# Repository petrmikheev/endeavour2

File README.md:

Endeavour2
==========

This is the second generation of my FPGA board.
Comparing to [endeavour1](https://github.com/petrmikheev/endeavour) it is 4 times faster and has 8x more memory.

The goal was the same as on the previous iteration -- to make a DIY computer based on FPGA. It should support display, keyboard, should be able to run Linux, should have on-device compiler toolchain, and ideally should be able to render some 3D graphic. It was fully achieved -- I have even managed to connect my board to WiFi and play Quake2 in multiplayer.

The project includes several parts:

- Hardware: design PCB and make the board. I ordered PCB manufacturing in JLCPCB, soldering is done manually.
- RTL: design SoC for my FPGA board. It is mostly assembled from open source IP cores, but some components are implemented from scratch.
- Firmware: written from scratch (except of integrated Dhrystone benchmark), includes initialization code, memtest, sbi implemetation, ext2 filesystem support, linux bootloader, built-in console. Provides some API (e.g printf) for software running in M-mode.
- Linux drivers for custom peripherals.
- Custom window manager and TTY implementation.

Note: This is a hobby project created just for fun. It doesn't have much practical use. However, if for some reason somebody wants to make a copy of this FPGA board, please let me know. I might add a bit more documentation.

Here's a story about how I worked on the project: **[https://blog.mikhe.ch/quake2-on-fpga](https://blog.mikhe.ch/quake2-on-fpga)**.

License: GPL-3.0 (except of footprints in hardware/endeavour2.pretty and Dhrystone benchmark in software/bios/dhrystone)

## Hardware

Main changes comparing to [endeavour1](https://github.com/petrmikheev/endeavour):

- This time I took a chance with BGA (Ball Grid Array) chips, and surprisingly soldering was not as hard as I expected.
- Using Efinix FPGA [Ti60F256](https://www.efinixinc.com/shop/ti60.php) with 60K logic cells and 256 1024x10b memory blocks. VexiiRiscv runs on this chip at frequency 207 MHz -- quite a lot for FPGA, especially in comparison to 60 MHz which I previously got with Altera Max10.
- 1GB DDR3 RAM IM8G16D3FFBG (against 128MB DDR1 in endeavour1). I use Efinix DDR3 Soft Controller Core. Using DDR3-400 mode, 800 MT/s, max theoretical throughput 1.6 GB/s. In practice in benchmarks I get up to 1.1 GB/s.
- Implemented SD Card voltage switch 3.3V/1.8V. In theory it allows to use UHS-1 cards in SDR104 mode (up to 100 MB/s), but for some cards writes failed at this speed, so I use SDR50 (46 MB/s in benchmark).
- Added a specialized TMDS encoder TFP410 (in endeavour1 video output was driven directly by FPGA pins which provided not enough current and caused green artifacts in some cases). Now all display modes with pixel rate up to 165 MHz are supported.
- More capacitors and a current limiting scheme on USB ports. USB hotplug can not cause device reset anymore!
- Added a real time clock in order not to appear in 1970 every time I start linux.
- Added ESP32 module as a WiFi adapter. `wget` shows download speed 926 KB/s.
- Added 2000mAh LiPo battery. 
- Added 4.2'' E-Ink display.

[KiCad project](hardware/board_2b), [gerber files](hardware/board_2b/production/endeavour2.zip).

**PCB production details ([JLCPCB](https://jlcpcb.com/capabilities/pcb-capabilities))**

- 6 layers
- Stackup: JLC06161H-3313
- Min via hole/diameter: 0.2/0.35mm
- Via covering: epoxy filled & capped

---

Endeavour2a (above) and Endeavour2b (below).

### Known design errors

In Endeavour2a:

- D+ and D- lines on USB-C port A are accidentally swapped, so port A can be used only as a power source. There are two USB-C ports because I was not sure that USB connection to PC will give enough power, and added a second USB-C for a power adapter. It turned out to be unnecessary, so in Endeavour2b the second port is removed.
- ESP32 connection scheme includes not all the pins which are needed for [ESP-Hosted-NG](https://github.com/espressif/esp-hosted/blob/master/esp_hosted_ng/README.md) firmware. I tried to remap some pins, but it caused extra delays and SPI transfers didn't work properly. So Endeavour2a has no WiFi. Fixed in Endeavour2b.

In Endeavour2b:

- Using same DC-DC converters as in Endeavour2a (TPS562211) to generate 0.95V, 1.35V, 1.8V. I forgot that it requires input power at least 4.2V and can work from USB (which was the case in Endeavour2a), but not from a battery pack. So the device can use battery power only when the battery is fully charged. Will be fixed in Endeavour2c.

### 3d printed case

---

## RTL

Used IP cores:

- [VexiiRiscv](https://github.com/SpinalHDL/VexiiRiscv/) - RISC-V core written in SpinalHDL.
- A few components distributed with [SpinalHDL](https://github.com/SpinalHDL/SpinalHDL) including Tilelink interconnect, APB3 bridge, USB OHCI controller, PLIC.
- [ZipCPU/sdspi SD-Card controller](https://github.com/ZipCPU/sdspi).
- [Efinix DDR3 Soft Controller Core](https://www.efinixinc.com/support/ip/ddr3-controller.php) (source not available, can be used only with Efinix FPGAs).

All the other components are designed from scratch.
DDR3 Tilelink adapter, UART controller, I2C controller, audio controller, SPI controllers (SPI FLASH, ESP32 SPI, and E2417 SPI interfaces have different requirements, so I end up with 3 different SPI controllers optimized for specific use cases), etc. Most notable are video controller and DMA controller.

[SpinalHDL](https://github.com/SpinalHDL/SpinalHDL) is being used to bring this all together.

### Video controller

- Has idependent text and graphic layers with transparency support.
- Configurable video timings.
- Supports both vertical (with wraparound) and horizontal panning.
- Graphic layer uses RGB565 format.
- Text layer has configurable charmap with 480 entries - e.g. ASCII + bold + italic variations + pseudographics can be loaded at the same time. Supports bitmap fonts with sizes from 8x8 to 8x16. Supports special 4-color symbols mode (used to render Endeavour logo, see screenshots below).
- APB3 control interface, Tilelink DMA interface.
- Implemented in verilog. [source](rtl/verilog/video_controller.v)
- There is [linux driver](software/linux/drivers/display.c). See usage in [include/endeavour2/display.h](software/include/endeavour2/display.h).

### DMA controller

- Can execute multiple memory operations by a single batch request from CPU (needed e.g. for hardware-accelerated window move in X11 since each line requires separate copying).
- Supports unaligned memset and memcpy (also essential for window move).
- Supports some graphics-related instructions: batched RGB565 mixing and palette mapping. So it is kind of a very primitive 2D GPU. I used it to speedup rendering in Quake2.
- APB3 control interface, Tilelink DMA interface.
- Implemented in SpinalHDL. [source](rtl/src/main/scala/endeavour2/DmaController.scala)

## Software

### [software/bios](software/bios)

Firmware. Initialization, benchmarks, sbi, bootloader, etc. Loaded on boot from SPI flash or via UART.

BIOS console allows to either boot OS (switches to supervisor mode), or inspect files (only EXT2 supported) and run binaries in machine mode.

BIOS provides API: [bios.h](software/include/endeavour2/raw/bios.h)

Example that uses this API: [hello_world.c](software/raw_examples/hello_world.c)

### [software/textwm2](software/textwm2)

Text-layer window manager and TTY implementation.

---

**wget 926 KB/s**, ESP32 as WiFi/BT adapter.

### [software/linux](software/linux)

Linux kernel config and drivers.

### [software/buildroot](software/buildroot)

Buildroot config and a few related scripts.

### [xdriver-endeavour2-fbdev](software/buildroot/xdriver-endeavour2-fbdev)

X11 driver which uses DMA controller when moving windows.

### [quake2sdl.patch](software/buildroot/quake2sdl.patch)

Patch for [quake2sdl](https://github.com/shamazmazum/quake2sdl).

- Using DMA controller for hardware-accelerated mapping from 256 colors to RGB565, and bilinear upscaling.
- Migrated from SDL audio to a custom endeavour2 driver with lower overhead (overhead of ALSA subsystem was quite significant).
- Downgraded from SDL2 to SDL1 (so it can run without X11).

Average FPS 12.2 on demo1 map with resolution 640x360 and bilinear upscaling to 1280x720.

### A few more screenshots

---

**DOOM**

---

**Quake 1**

---

**Heroes2**

---

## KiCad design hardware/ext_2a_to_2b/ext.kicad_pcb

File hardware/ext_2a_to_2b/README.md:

It is extension for `board_2a` to test some parts of `board_2b` schematics

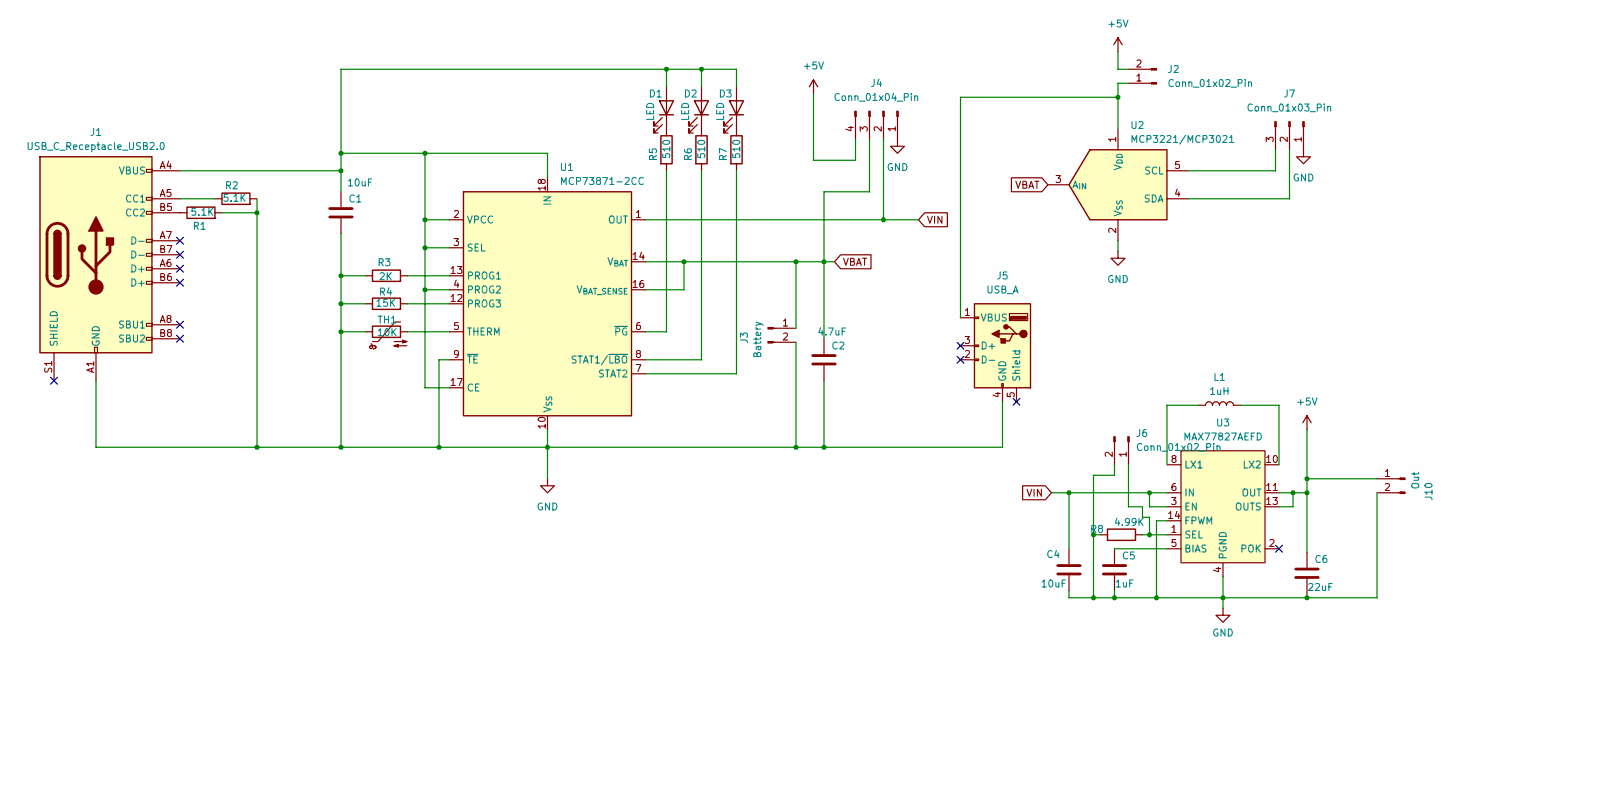
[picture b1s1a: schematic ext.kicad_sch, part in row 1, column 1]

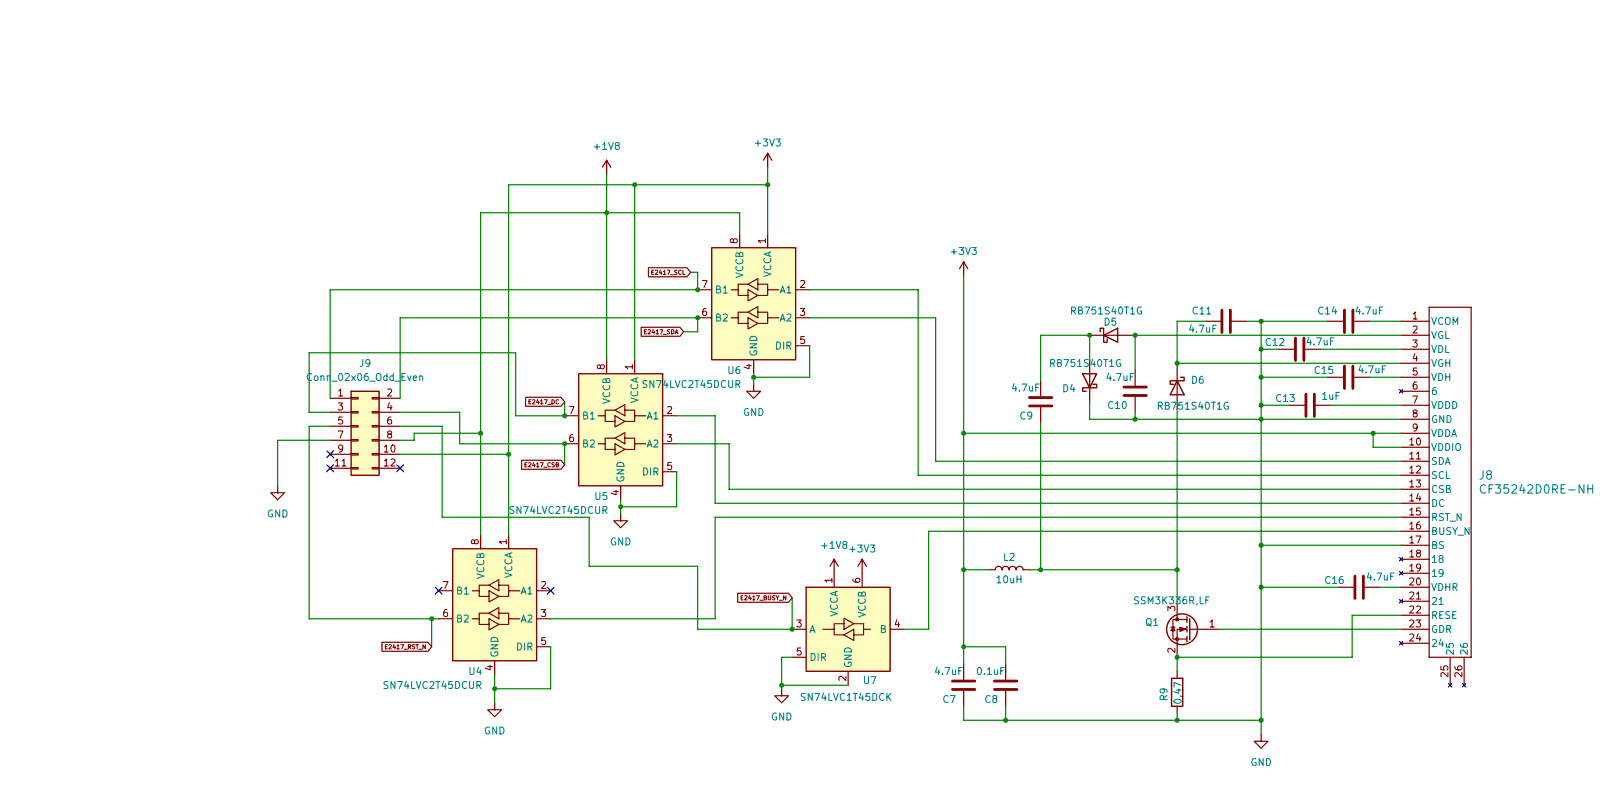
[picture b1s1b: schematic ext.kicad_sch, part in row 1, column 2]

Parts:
C1, C4: 10uF; C_0603_1608Metric
C2, C7, C9, C10, C11, C12, C14, C15, C16: 4.7uF; C_0603_1608Metric
C5, C13: 1uF; C_0603_1608Metric
C6: 22uF; C_0805_2012Metric
C8: 0.1uF; C_0603_1608Metric
D1, D2, D3: LED; LED_0603_1608Metric
D4, D5, D6: RB751S40T1G; D_SOD-523
J1: USB_C_Receptacle_USB2.0; USB_C_Receptacle_GCT_USB4105-xx-A_16P_TopMnt_Horizontal
J2, J6: Conn_01x02_Pin; PinHeader_1x02_P2.54mm_Vertical
J3: Battery; JST_B2B-PH-SM4-TB
J4: Conn_01x04_Pin; PinHeader_1x04_P2.54mm_Vertical
J5: USB_A; USB_A_Receptacle_GCT_USB1046
J7: Conn_01x03_Pin; PinHeader_1x03_P2.54mm_Vertical
J8: CF35242D0RE-NH; CONN24X1_CF35242D0RE-NH_CVI
J9: Conn_02x06_Odd_Even; PinHeader_2x06_P2.54mm_Vertical
J10: Out; JST_B2B-PH-SM4-TB
L1: 1uH; L_0805_2012Metric
L2: 10uH; L_0805_2012Metric
Q1: SSM3K336R,LF; SOT-23-3
R1, R2: 5.1K; R_0603_1608Metric
R3: 2K; R_0603_1608Metric
R4: 15K; R_0603_1608Metric
R5, R6, R7: 510; R_0603_1608Metric
R8: 4.99K; R_0603_1608Metric
R9: 0.47; R_0603_1608Metric
TH1: 10K; R_0603_1608Metric
U1: MCP73871-2CC; QFN-20-1EP_4x4mm_P0.5mm_EP2.5x2.5mm
U2: MCP3221/MCP3021; SOT-23-5
U3: MAX77827AEFD; Maxim_FC2QFN-14_2.5x2.5mm_P0.5mm
U4, U5, U6: SN74LVC2T45DCUR; VSSOP-8_2.3x2mm_P0.5mm
U7: SN74LVC1T45DCK; SOT-363_SC-70-6

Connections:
+1V8: J9.8, U4.8 (VCCB), U5.8 (VCCB), U6.8 (VCCB), U7.1 (VCCA)
+3V3: C7.2, C8.2, J8.9 (VDDA), J8.10 (VDDIO), J9.10, L2.1, U4.1 (VCCA), U5.1 (VCCA), U6.1 (VCCA), U7.6 (VCCB)
+5V: C6.1, J2.2, J4.4, J10.1, U3.11 (OUT), U3.13 (OUTS)
E2417_BUSY_N: J9.6, U7.3 (A)
E2417_CSB: J9.4, U5.6 (B2)
E2417_DC: J9.3, U5.7 (B1)
E2417_RST_N: J9.5, U4.6 (B2)
E2417_SCL: J9.1, U6.7 (B1)
E2417_SDA: J9.2, U6.6 (B2)
GND: C1.2, C2.2, C4.2, C5.2, C6.2, C7.1, C8.1, C10.1, C11.1, C12.1, C13.1, C14.1, C15.1, C16.1, D4.1 (K), J1.A1 (GND), J1.A12 (GND), J1.B1 (GND), J1.B12 (GND), J3.2, J4.1, J5.4 (GND), J6.2, J7.1, J8.8 (GND), J8.17 (BS), J9.7, J10.2, R1.2, R2.2, R3.1, R4.1, R8.1, R9.1, TH1.1, U1.9 (~TE), U1.10 (V_{SS}), U1.11 (V_{SS}), U1.21 (V_{SS}), U2.2 (V_{SS}), U3.4 (PGND), U3.9 (PGND), U3.14 (FPWM), U4.4 (GND), U4.5 (DIR), U5.4 (GND), U5.5 (DIR), U6.4 (GND), U6.5 (DIR), U7.2 (GND), U7.5 (DIR)
unnamed: C1.1, D1.2 (A), D2.2 (A), D3.2 (A), J1.A4 (VBUS), J1.A9 (VBUS), J1.B4 (VBUS), J1.B9 (VBUS), U1.2 (VPCC), U1.3 (SEL), U1.4 (PROG2), U1.17 (CE), U1.18 (IN), U1.19 (IN)
unnamed: D1.1 (K), R5.1
unnamed: D2.1 (K), R6.1
unnamed: D3.1 (K), R7.1
unnamed: C9.2, D4.2 (A), D5.1 (K)
unnamed: C10.2, D5.2 (A), J8.2 (VGL)
unnamed: C9.1, D6.2 (A), L2.2, Q1.3 (D)
unnamed: C11.2, D6.1 (K), J8.4 (VGH)
unnamed: J1.A5 (CC1), R2.1
unnamed: J1.B5 (CC2), R1.1
unnamed: J2.1, J5.1 (VBUS), U2.1 (V_{DD})
unnamed: J6.1, R8.2, U3.1 (SEL)
unnamed: J7.2, U2.4 (SDA)
unnamed: J7.3, U2.5 (SCL)
unnamed: J8.16 (BUSY_N), U7.4 (B)
unnamed: J8.13 (CSB), U5.3 (A2)
unnamed: J8.14 (DC), U5.2 (A1)
unnamed: J8.23 (GDR), Q1.1 (G)
unnamed: J8.22 (RESE), Q1.2 (S), R9.2
unnamed: J8.15 (RST_N), U4.3 (A2)
unnamed: J8.12 (SCL), U6.2 (A1)
unnamed: J8.11 (SDA), U6.3 (A2)
unnamed: C14.2, J8.1 (VCOM)
unnamed: C13.2, J8.7 (VDDD)
unnamed: C15.2, J8.5 (VDH)
unnamed: C16.2, J8.20 (VDHR)
unnamed: C12.2, J8.3 (VDL)
unnamed: R3.2, U1.13 (PROG1)
unnamed: R4.2, U1.12 (PROG3)
unnamed: R6.2, U1.8 (STAT1/~LBO)
unnamed: R7.2, U1.7 (STAT2)
unnamed: TH1.2, U1.5 (THERM)
unnamed: R5.2, U1.6 (~PG)
unnamed: C5.1, U3.5 (BIAS)
unnamed: L1.1, U3.8 (LX1)
unnamed: L1.2, U3.10 (LX2)
VBAT: C2.1, J3.1, J4.3, U1.14 (V_{BAT}), U1.15 (V_{BAT}), U1.16 (V_{BAT_SENSE}), U2.3 (A_{IN})
VIN: C4.1, J4.2, U1.1 (OUT), U1.20 (OUT), U3.3 (EN), U3.6 (IN)

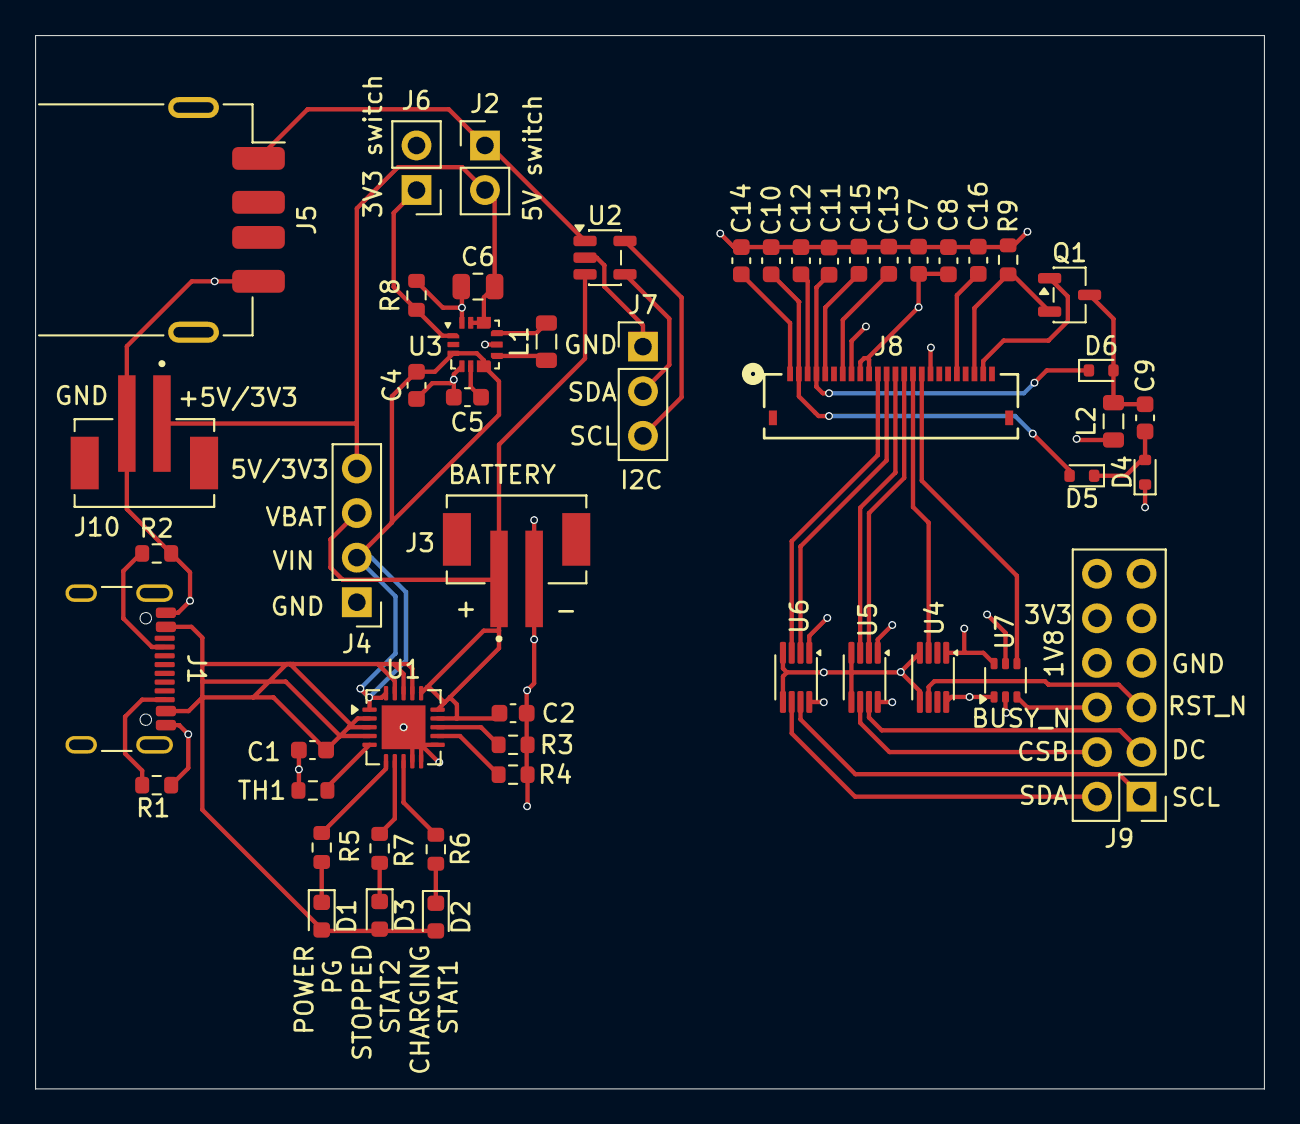
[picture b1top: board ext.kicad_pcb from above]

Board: 4 copper layers, 70.0 x 60.0 mm, 51 parts (0 on the bottom side), 48 nets.

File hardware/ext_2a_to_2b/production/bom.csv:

Designator,Footprint,Quantity,Value,LCSC Part #
"C1, C4",0603,2,10uF,
"C10, C11, C12, C14, C15, C16, C2, C7, C9",0603,9,4.7uF,
"C13, C5",0603,2,1uF,
C6,0805,1,22uF,
C8,0603,1,0.1uF,
"D1, D2, D3",0603,3,LED,
"D4, D5, D6",D_SOD-523,3,RB751S40T1G,
J1,USB_C_Receptacle_GCT_USB4105-xx-A_16P_TopMnt_Horizontal,1,USB_C_Receptacle_USB2.0,
J10,JST_B2B-PH-SM4-TB,1,Out,
"J2, J6",PinHeader_1x02_P2.54mm_Vertical,2,Conn_01x02_Pin,
J3,JST_B2B-PH-SM4-TB,1,Battery,
J4,PinHeader_1x04_P2.54mm_Vertical,1,Conn_01x04_Pin,
J5,USB_A_Receptacle_GCT_USB1046,1,USB_A,
J7,PinHeader_1x03_P2.54mm_Vertical,1,Conn_01x03_Pin,
J8,CONN24X1_CF35242D0RE-NH_CVI,1,CF35242D0RE-NH,
J9,PinHeader_2x06_P2.54mm_Vertical,1,Conn_02x06_Odd_Even,
L1,0805,1,1uH,
L2,0805,1,10uH,
Q1,SOT-23-3,1,"SSM3K336R,LF",
"R1, R2",0603,2,5.1K,
R3,0603,1,2K,
R4,0603,1,15K,
"R5, R6, R7",0603,3,510,
R8,0603,1,4.99K,
R9,0603,1,0.47,
TH1,0603,1,10K,
U1,QFN-20-1EP_4x4mm_P0.5mm_EP2.5x2.5mm,1,MCP73871-2CC,
U2,SOT-23-5,1,MCP3221/MCP3021,
U3,Maxim_FC2QFN-14_2.5x2.5mm_P0.5mm,1,MAX77827AEFD,
"U4, U5, U6",VSSOP-8_2.3x2mm_P0.5mm,3,SN74LVC2T45DCUR,
U7,SOT-363_SC-70-6,1,SN74LVC1T45DCK,

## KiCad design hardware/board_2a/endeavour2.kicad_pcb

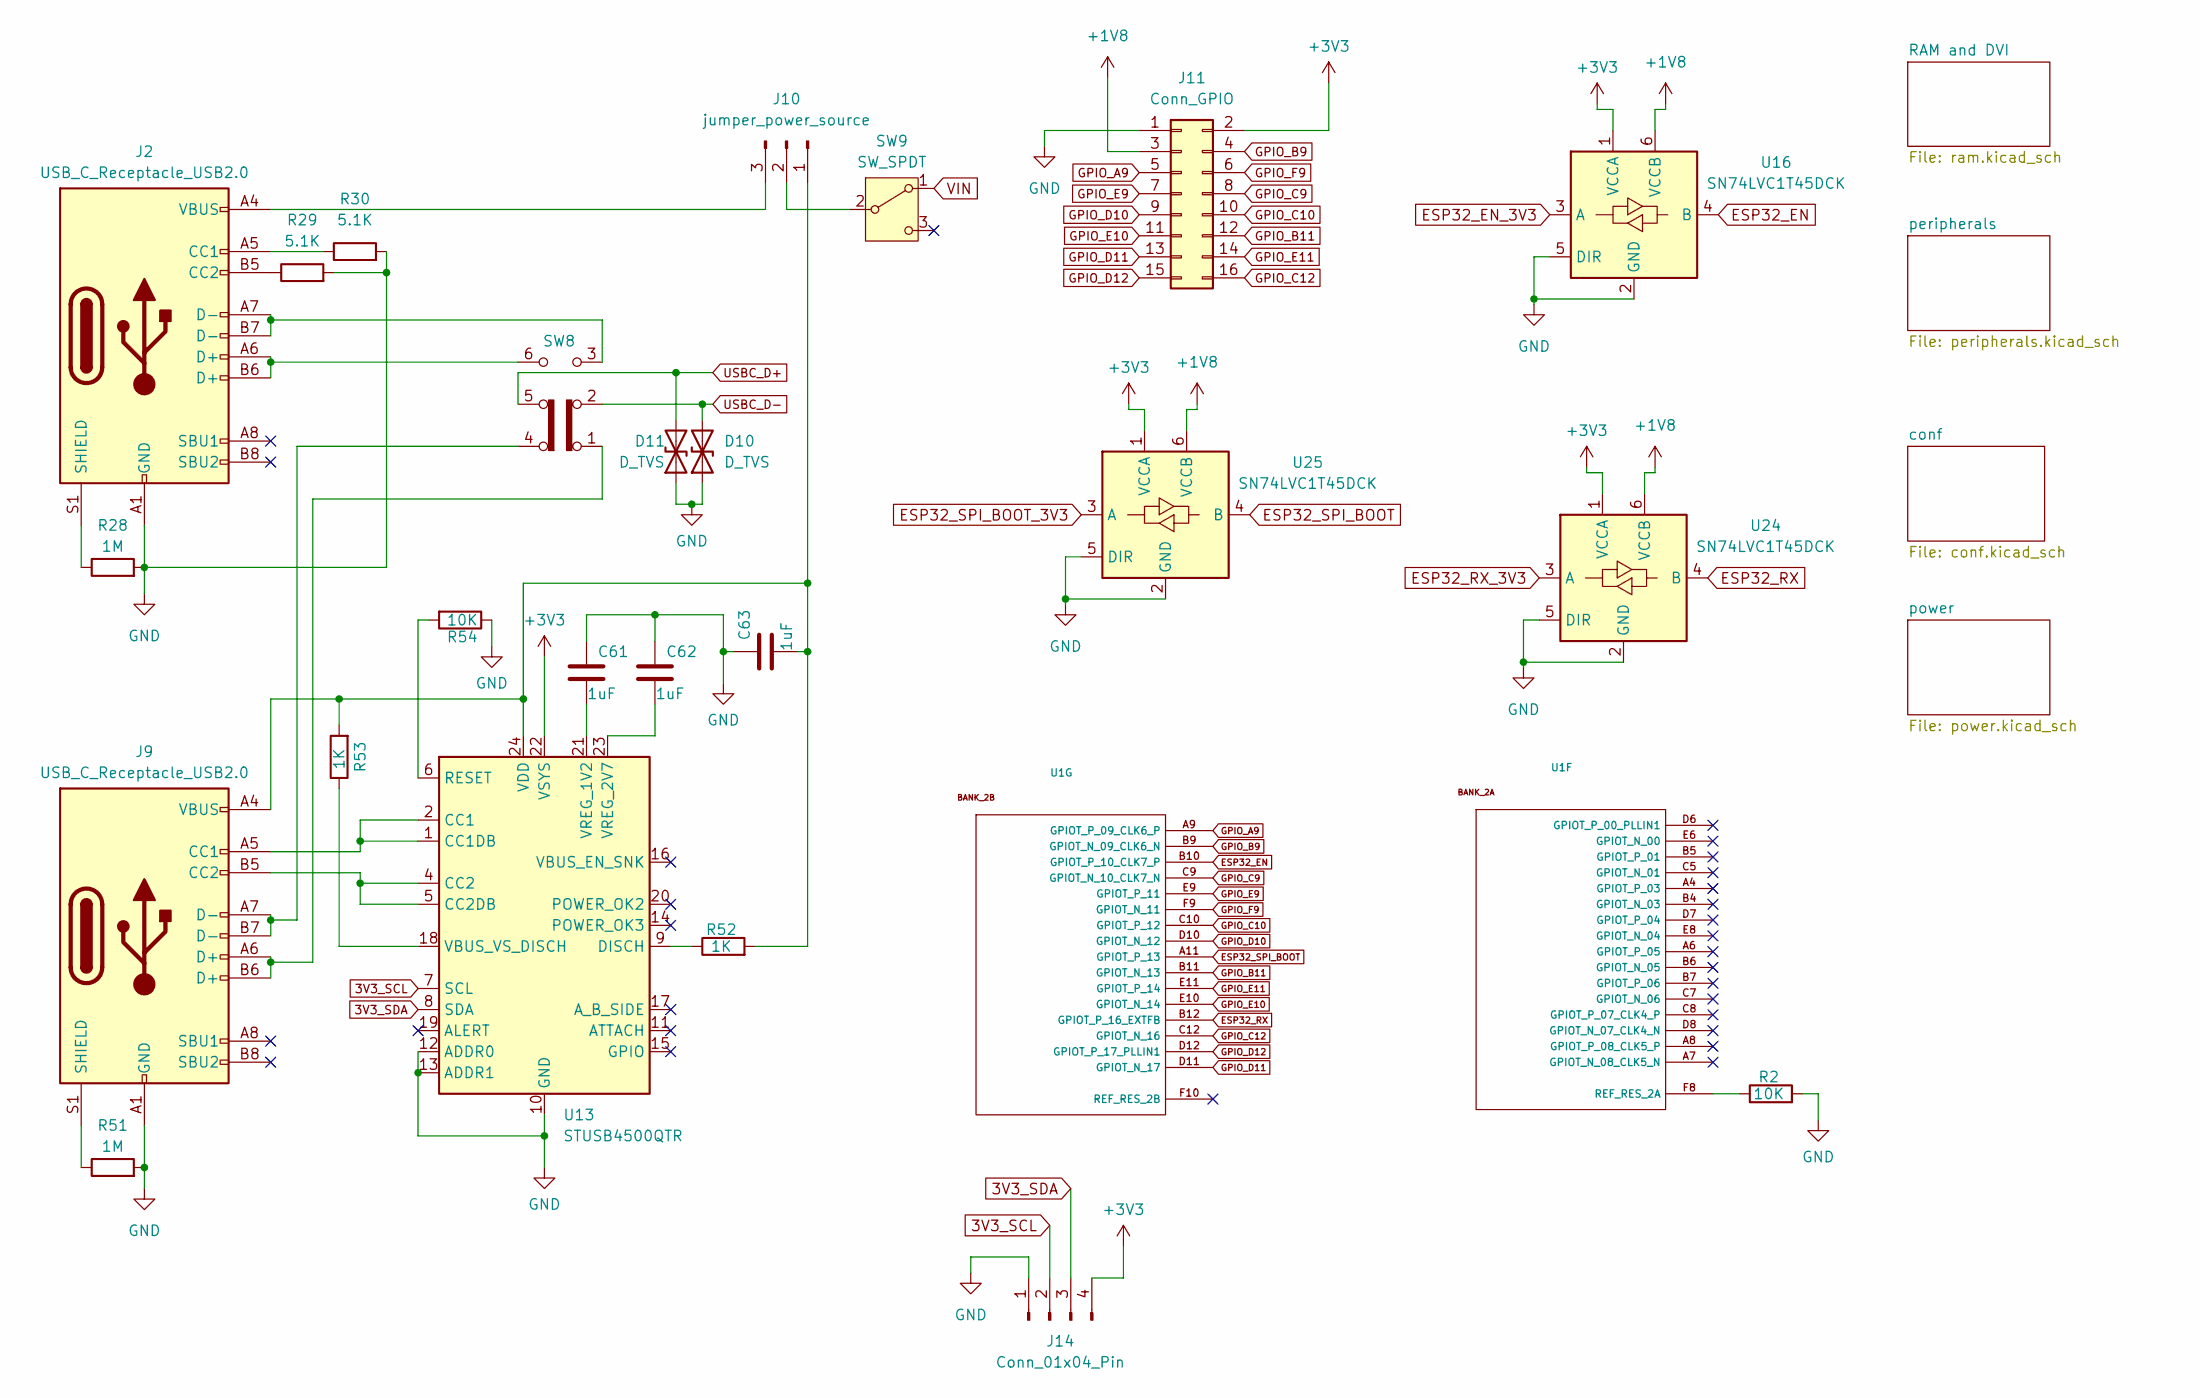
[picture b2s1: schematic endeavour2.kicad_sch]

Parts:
C61, C62, C63: 1uF; C_0603_1608Metric
D10, D11: D_TVS; D_0603_1608Metric
J2, J9: USB_C_Receptacle_USB2.0; USB_C_Receptacle_GCT_USB4105-xx-A_16P_TopMnt_Horizontal
J10: jumper_power_source; PinHeader_1x03_P2.54mm_Vertical
J11: Conn_GPIO; PinHeader_2x08_P2.54mm_Vertical
J14: Conn_01x04_Pin; PinHeader_1x04_P2.54mm_Vertical
R2, R54: 10K; R_0603_1608Metric
R28, R51: 1M; R_0603_1608Metric
R29, R30: 5.1K; R_0603_1608Metric
R52, R53: 1K; R_0603_1608Metric
SW8: SW_JS202011SCQN
SW9: SW_SPDT; mss3111
U1: Ti60F256; BGA-256_14.0x14.0mm_Layout16x16_P0.8mm_Ball0.45mm_Pad0.32mm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
U13: STUSB4500QTR; QFN-24-1EP_4x4mm_P0.5mm_EP2.7x2.7mm
U16, U24, U25: SN74LVC1T45DCK; SOT-363_SC-70-6

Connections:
3V3_SCL: J14.2, U13.7 (SCL); also elsewhere on the board
3V3_SDA: J14.3, U13.8 (SDA); also elsewhere on the board
+1V8: J11.3, U16.6 (VCCB), U24.6 (VCCB), U25.6 (VCCB); also elsewhere on the board
+3V3: J11.2, J14.4, U13.22 (VSYS), U16.1 (VCCA), U24.1 (VCCA), U25.1 (VCCA); also elsewhere on the board
ESP32_EN: U1.B10 (GPIOT_P_10_CLK7_P), U16.4 (B)
ESP32_EN_3V3: U16.3 (A); also elsewhere on the board
ESP32_RX: U1.B12 (GPIOT_P_16_EXTFB), U24.4 (B)
ESP32_RX_3V3: U24.3 (A); also elsewhere on the board
ESP32_SPI_BOOT: U1.A11 (GPIOT_P_13), U25.4 (B)
ESP32_SPI_BOOT_3V3: U25.3 (A); also elsewhere on the board
GND: C61.1, C62.1, C63.1, D10.1 (A1), D11.1 (A1), J2.A1 (GND), J2.A12 (GND), J2.B1 (GND), J2.B12 (GND), J9.A1 (GND), J9.A12 (GND), J9.B1 (GND), J9.B12 (GND), J11.1, J14.1, R2.2, R28.2, R29.2, R30.2, R51.2, R54.1, U13.10 (GND), U13.12 (ADDR0), U13.13 (ADDR1), U13.25 (GND), U16.2 (GND), U16.5 (DIR), U24.2 (GND), U24.5 (DIR), U25.2 (GND), U25.5 (DIR); also elsewhere on the board
GPIO_A9: J11.5, U1.A9 (GPIOT_P_09_CLK6_P)
GPIO_B9: J11.4, U1.B9 (GPIOT_N_09_CLK6_N)
GPIO_B11: J11.12, U1.B11 (GPIOT_N_13)
GPIO_C9: J11.8, U1.C9 (GPIOT_N_10_CLK7_N)
GPIO_C10: J11.10, U1.C10 (GPIOT_P_12)
GPIO_C12: J11.16, U1.C12 (GPIOT_N_16)
GPIO_D10: J11.9, U1.D10 (GPIOT_N_12)
GPIO_D11: J11.13, U1.D11 (GPIOT_N_17)
GPIO_D12: J11.15, U1.D12 (GPIOT_P_17_PLLIN1)
GPIO_E9: J11.7, U1.E9 (GPIOT_P_11)
GPIO_E10: J11.11, U1.E10 (GPIOT_N_14)
GPIO_E11: J11.14, U1.E11 (GPIOT_P_14)
GPIO_F9: J11.6, U1.F9 (GPIOT_N_11)
unnamed: J2.A5 (CC1), R30.1
unnamed: J2.B5 (CC2), R29.1
unnamed: J2.A6 (D+), J2.B6 (D+), SW8.6 (A)
unnamed: J2.A7 (D-), J2.B7 (D-), SW8.3 (C)
unnamed: J2.S1 (SHIELD), R28.1
unnamed: J9.A5 (CC1), U13.1 (CC1DB), U13.2 (CC1)
unnamed: J9.B5 (CC2), U13.4 (CC2), U13.5 (CC2DB)
unnamed: J9.A6 (D+), J9.B6 (D+), SW8.1 (A)
unnamed: J9.A7 (D-), J9.B7 (D-), SW8.4 (C)
unnamed: J9.S1 (SHIELD), R51.1
unnamed: C63.2, J9.A4 (VBUS), J9.A9 (VBUS), J9.B4 (VBUS), J9.B9 (VBUS), J10.1, R52.2, R53.2, U13.24 (VDD)
unnamed: J10.2, SW9.2 (B)
unnamed: J2.A4 (VBUS), J2.A9 (VBUS), J2.B4 (VBUS), J2.B9 (VBUS), J10.3
unnamed: R2.1, U1.F8 (REF_RES_2A)
unnamed: R52.1, U13.9 (DISCH)
unnamed: R54.2, U13.6 (RESET)
unnamed: R53.1, U13.18 (VBUS_VS_DISCH)
unnamed: C61.2, U13.21 (VREG_1V2)
unnamed: C62.2, U13.23 (VREG_2V7)
USBC_D+: D11.2 (A2), SW8.5 (B); also elsewhere on the board
USBC_D-: D10.2 (A2), SW8.2 (B); also elsewhere on the board
VIN: SW9.1 (A); also elsewhere on the board

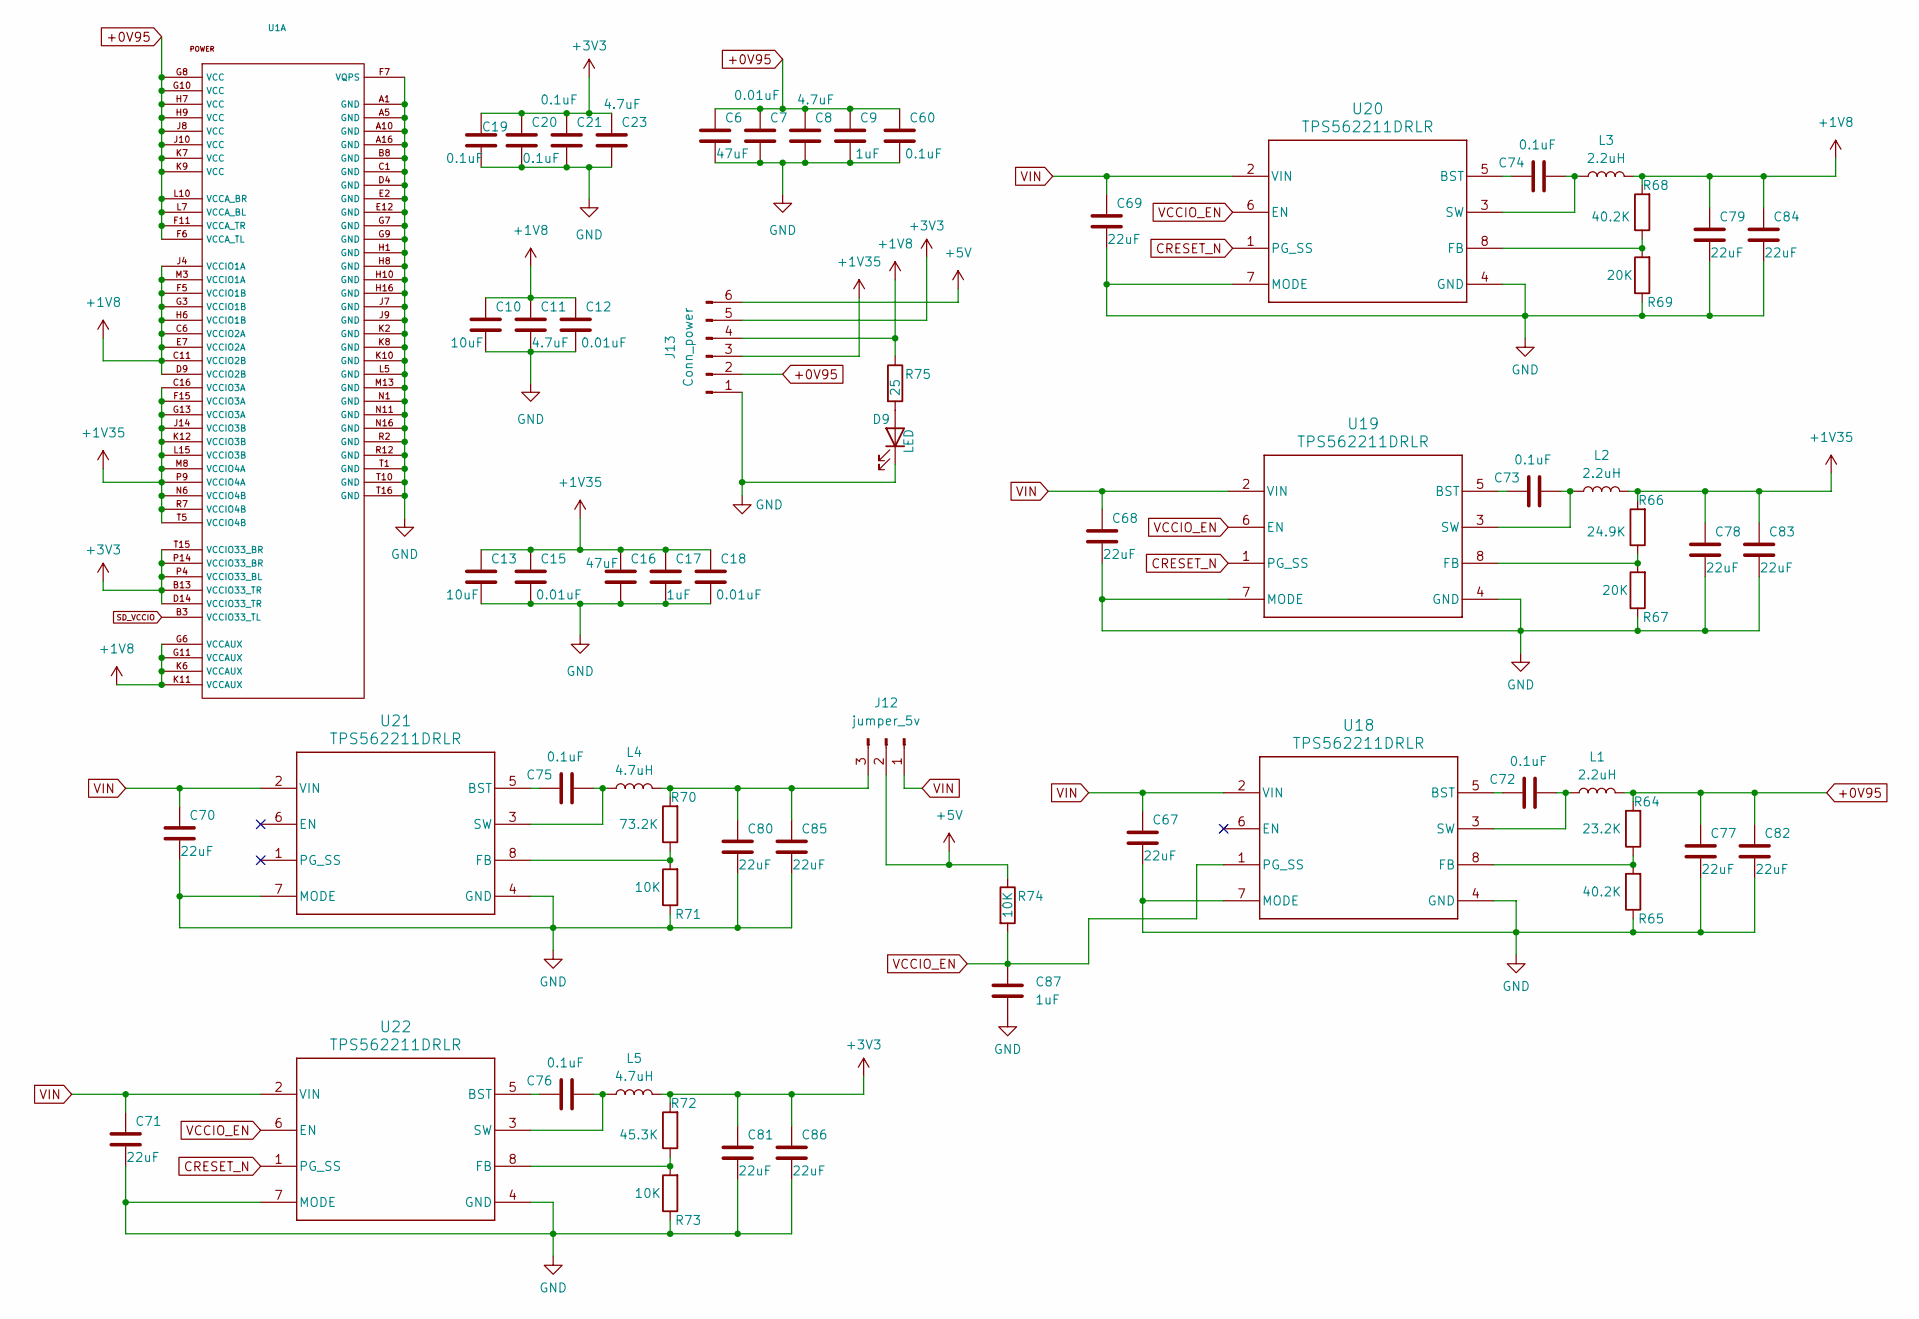
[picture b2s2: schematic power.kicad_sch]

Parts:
C6, C16: 47uF; C_0603_1608Metric
C7, C12, C15, C18: 0.01uF; C_0603_1608Metric
C8, C11, C23: 4.7uF; C_0603_1608Metric
C9, C17, C87: 1uF; C_0603_1608Metric
C10, C13: 10uF; C_0603_1608Metric
C19, C20, C21, C60, C72, C73, C74, C75, C76: 0.1uF; C_0603_1608Metric
C67, C68, C69, C70, C71, C77, C78, C79, C80, C81, C82, C83, C84, C85, C86: 22uF; C_0805_2012Metric
D9: LED; LED_0603_1608Metric
J12: jumper_5v; PinHeader_1x03_P2.54mm_Vertical
J13: Conn_power; PinHeader_1x06_P2.54mm_Vertical
L1, L2, L3: 2.2uH; L_1008_2520Metric
L4, L5: 4.7uH; L_1008_2520Metric
R64: 23.2K; R_0603_1608Metric
R65, R68: 40.2K; R_0603_1608Metric
R66: 24.9K; R_0603_1608Metric
R67, R69: 20K; R_0603_1608Metric
R70: 73.2K; R_0603_1608Metric
R71, R73, R74: 10K; R_0603_1608Metric
R72: 45.3K; R_0603_1608Metric
R75: 25; R_0603_1608Metric
U1: Ti60F256; BGA-256_14.0x14.0mm_Layout16x16_P0.8mm_Ball0.45mm_Pad0.32mm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
U18, U19, U20, U21, U22: TPS562211DRLR; DRL0008A-MFG

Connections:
+0V95: C6.1, C7.1, C8.1, C9.1, C60.1, C77.1, C82.1, J13.2, L1.2, R64.2, U1.F6 (VCCA_TL), U1.F11 (VCCA_TR), U1.G8 (VCC), U1.G10 (VCC), U1.H7 (VCC), U1.H9 (VCC), U1.J8 (VCC), U1.J10 (VCC), U1.K7 (VCC), U1.K9 (VCC), U1.L7 (VCCA_BL), U1.L10 (VCCA_BR)
+1V8: C10.1, C11.1, C12.1, C79.1, C84.1, J13.4, L3.2, R68.2, R75.1, U1.C6 (VCCIO2A), U1.C11 (VCCIO2B), U1.D9 (VCCIO2B), U1.E7 (VCCIO2A), U1.F5 (VCCIO1B), U1.G3 (VCCIO1B), U1.G6 (VCCAUX), U1.G11 (VCCAUX), U1.H6 (VCCIO1B), U1.J4 (VCCIO1A), U1.K6 (VCCAUX), U1.K11 (VCCAUX), U1.M3 (VCCIO1A); also elsewhere on the board
+1V35: C13.1, C15.1, C16.1, C17.1, C18.1, C78.1, C83.1, J13.3, L2.2, R66.2, U1.C16 (VCCIO3A), U1.F15 (VCCIO3A), U1.G13 (VCCIO3A), U1.J14 (VCCIO3B), U1.K12 (VCCIO3B), U1.L15 (VCCIO3B), U1.M8 (VCCIO4A), U1.N6 (VCCIO4B), U1.P9 (VCCIO4A), U1.R7 (VCCIO4B), U1.T5 (VCCIO4B); also elsewhere on the board
+3V3: C19.1, C20.1, C21.1, C23.1, C81.1, C86.1, J13.5, L5.2, R72.2, U1.B13 (VCCIO33_TR), U1.D14 (VCCIO33_TR), U1.P4 (VCCIO33_BL), U1.P14 (VCCIO33_BR), U1.T15 (VCCIO33_BR); also elsewhere on the board
+5V: J12.2, J13.6, R74.1; also elsewhere on the board
CRESET_N: U19.1 (PG_SS), U20.1 (PG_SS), U22.1 (PG_SS); also elsewhere on the board
GND: C6.2, C7.2, C8.2, C9.2, C10.2, C11.2, C12.2, C13.2, C15.2, C16.2, C17.2, C18.2, C19.2, C20.2, C21.2, C23.2, C60.2, C67.2, C68.2, C69.2, C70.2, C71.2, C77.2, C78.2, C79.2, C80.2, C81.2, C82.2, C83.2, C84.2, C85.2, C86.2, C87.2, D9.1 (K), J13.1, R65.1, R67.1, R69.1, R71.1, R73.1, U1.A1 (GND), U1.A5 (GND), U1.A10 (GND), U1.A16 (GND), U1.B8 (GND), U1.C1 (GND), U1.D4 (GND), U1.E2 (GND), U1.E12 (GND), U1.F7 (VQPS), U1.G7 (GND), U1.G9 (GND), U1.H1 (GND), U1.H8 (GND), U1.H10 (GND), U1.H16 (GND), U1.J7 (GND), U1.J9 (GND), U1.K2 (GND), U1.K8 (GND), U1.K10 (GND), U1.L5 (GND), U1.M13 (GND), U1.N1 (GND), U1.N11 (GND), U1.N16 (GND), U1.R2 (GND), U1.R12 (GND), U1.T1 (GND), U1.T10 (GND), U1.T16 (GND), U18.4 (GND), U18.7 (MODE), U19.4 (GND), U19.7 (MODE), U20.4 (GND), U20.7 (MODE), U21.4 (GND), U21.7 (MODE), U22.4 (GND), U22.7 (MODE); also elsewhere on the board
unnamed: D9.2 (A), R75.2
unnamed: C80.1, C85.1, J12.3, L4.2, R70.2
unnamed: C72.1, U18.5 (BST)
unnamed: R64.1, R65.2, U18.8 (FB)
unnamed: C72.2, L1.1, U18.3 (SW)
unnamed: C73.1, U19.5 (BST)
unnamed: R66.1, R67.2, U19.8 (FB)
unnamed: C73.2, L2.1, U19.3 (SW)
unnamed: C74.1, U20.5 (BST)
unnamed: R68.1, R69.2, U20.8 (FB)
unnamed: C74.2, L3.1, U20.3 (SW)
unnamed: C75.1, U21.5 (BST)
unnamed: R70.1, R71.2, U21.8 (FB)
unnamed: C75.2, L4.1, U21.3 (SW)
unnamed: C76.1, U22.5 (BST)
unnamed: R72.1, R73.2, U22.8 (FB)
unnamed: C76.2, L5.1, U22.3 (SW)
SD_VCCIO: U1.B3 (VCCIO33_TL); also elsewhere on the board
VCCIO_EN: C87.1, R74.2, U18.1 (PG_SS), U19.6 (EN), U20.6 (EN), U22.6 (EN)
VIN: C67.1, C68.1, C69.1, C70.1, C71.1, J12.1, U18.2 (VIN), U19.2 (VIN), U20.2 (VIN), U21.2 (VIN), U22.2 (VIN); also elsewhere on the board
